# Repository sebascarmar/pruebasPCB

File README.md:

# pruebasPCB

## IMPRESION DE FOTOLITO:
	* Primero se imprime en papel común el circuito en negativo: con ahorro de toner,
	con 100 de brillo y 0 de contraste.

	* Arriba de esa impresión se pone un pedazo de papel vegetal.

	* Se configura la impresora para papel THICK, sin ahorro de toner, 0 de brillo y 110 
	de contraste.

	* Luego se lo pone ENNEGRECEDOR DE TONER al fotolito de papel vegetal, y se lo deja 
	secar.

	* En caso de ser necesario, se imprimen 2 fotolitos, ya que la rigidez del papel
	vegetal permite alinearlos fácilmente.

## FILM:
	* El film se separa con cinta schotch de forma fácil.

	* El film se pone con agua, se alisa y luego se le pone calor. Se cortan los bordes,
	se le da un poco más de calor,y se alisa una vez más.

	* Se le pone el fotolito, se pone entre vidrios y se cura por 20 seg.

	* Se deja por 2 min en el revelador, ayudando con un cepillo.

	* Si se ven algunas arrugas en el curado, las pistas saldrán cortadas. Descartar.
	
## ATACADO DE COBRE:
	* Luego del ataque químico al cobre (5 min), se pone en el removedor durante 2 min
	y listo.
	
## MÁSCARA:
	* Se imprime la máscara de soldado con expansión de 0.3 mm (desde board setup). Debe
	ser la misma forma en la que se hizo el fotolito del circuito.

	* Se corta De forma tal que le queden "orejas".

	* Se corta un pedazo de acetato que tenga orejas más grandes que el fotolito, y se expande 
	la pintura lo mejor posible.

	* Se pega delicadamente el fotolito al acetato de ambos lados de las orejas, de forma que 
	quede BIEN ALINEADO.

	* Se cura durante 4 minutos, tiempo suficente para poder sacarla y limpiarle la 
	máscara no curada (la de los pads). 

	* Luego se puede dejar curando el tiempo que sea necesario.

	* Se recomienda usar guantes, la máscara uv cuesta sacarla.
	
## SERIGRAFÍA:
	* Imrpimirla en una hoja común.

	* Cortarlo de manera que le queden dos "orejas".

	* Se alinea con la placa, y de una de las orejas se pega a la placa.

	* Con quitaesmalte ALGABO amarillo, mojar la placa y poner la hoja encima de la misma

	* Durante 2 minutos, dejando siempre mojado, y presionar con rodillo y dedos.

	* Retirar el papel estando aun mojado el papel.

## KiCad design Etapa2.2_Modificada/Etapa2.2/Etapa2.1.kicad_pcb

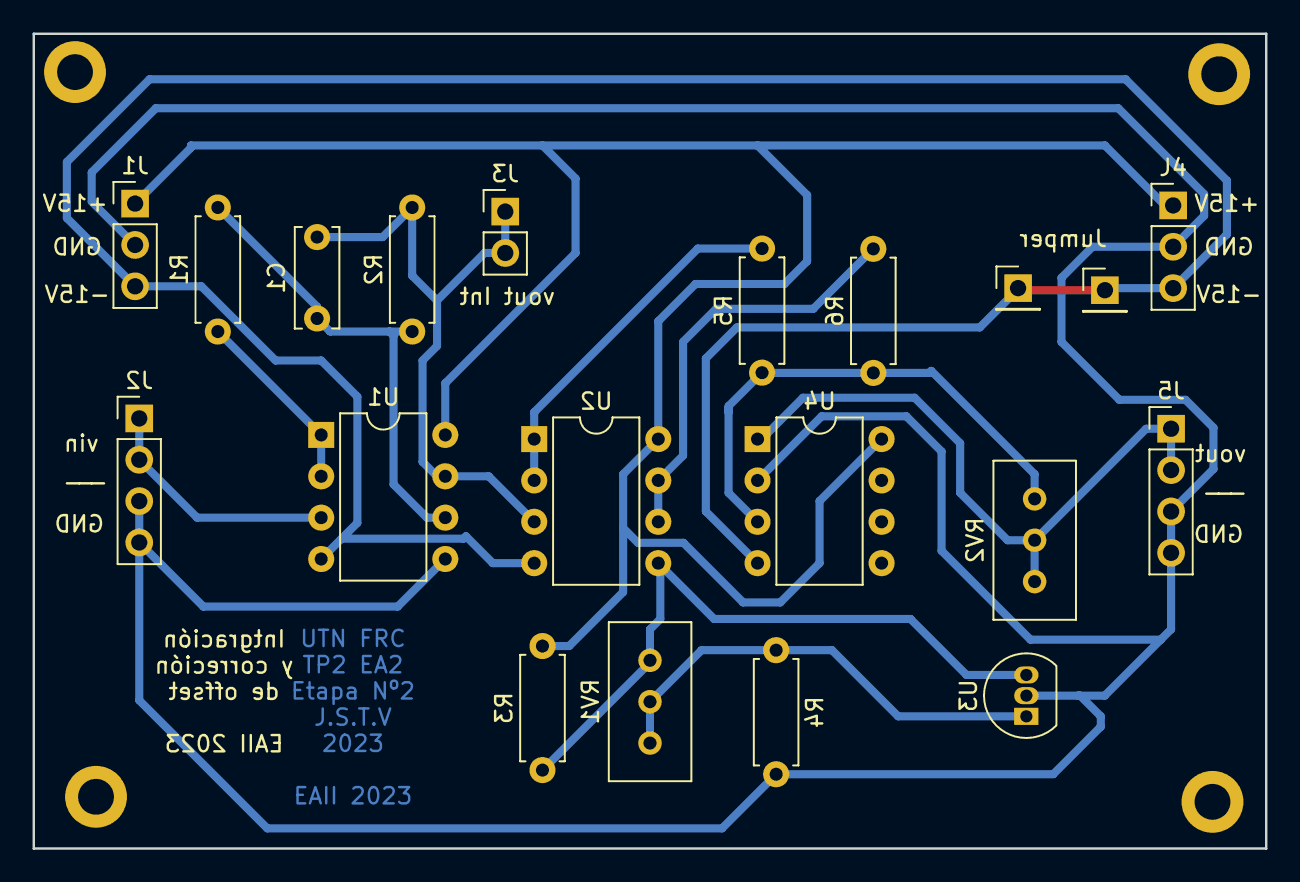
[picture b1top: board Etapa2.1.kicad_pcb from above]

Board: 2 copper layers, 75.7 x 50.0 mm, 19 parts (0 on the bottom side), 13 nets.

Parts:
C1: 10n; C_Disc_D6.0mm_W2.5mm_P5.00mm
J1: Conn_VinDC; PinHeader_1x03_P2.54mm_Vertical
J2: Conn_Vin; PinHeader_1x04_P2.54mm_Vertical
J3: Conn_VoutInteg; PinHeader_1x02_P2.54mm_Vertical
J4: Conn_VoutDC; PinHeader_1x03_P2.54mm_Vertical
J5: Conn_Vout; PinHeader_1x04_P2.54mm_Vertical
Jumper: PinHeader_1x01_P2.54mm_Vertical
R1, R3, R4, R5, R6: 10k; R_Axial_DIN0207_L6.3mm_D2.5mm_P7.62mm_Horizontal
R2: 100k; R_Axial_DIN0207_L6.3mm_D2.5mm_P7.62mm_Horizontal
RV1: 10k; Potentiometer_Bourns_3296W_Vertical
RV2: 50k; Potentiometer_Bourns_3296W_Vertical
U1, U2, U4: TL082; DIP-8_W7.62mm
U3: TL431LP; TO-92_Inline

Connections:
+15V: J1.1, J4.1, R3.2, U1.8 (V+), U2.8 (V+), U4.8 (V+)
-15V: J1.3, J4.3, U1.4 (V-), U2.4 (V-), U4.4 (V-)
GND: J1.2, J2.3, J2.4, J4.2, J5.3, J5.4, R4.2, U1.5 (+), U3.2 (A), U4.2 (-)
unnamed: R1.1, U1.1, U1.2 (-)
unnamed: C1.1, R1.2, R2.1, U1.6 (-)
unnamed: R5.2, U2.1, U2.2 (-)
unnamed: R3.1, RV1.1, U2.5 (+), U3.3 (K)
unnamed: R6.2, U2.6 (-), U2.7
unnamed: R4.1, RV1.2, RV1.3, U3.1 (REF)
unnamed: R5.1, R6.1, RV2.1, U4.3 (+)
Vin2: J2.1, J2.2, U1.3 (+)
Vout2: J5.1, J5.2, RV2.2, RV2.3, U4.1
Vout_Integ: C1.2, J3.1, J3.2, R2.2, U1.7, U2.3 (+)

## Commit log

2024-03-18 Agrega archivos
2024-03-18 Corrige formato de items
